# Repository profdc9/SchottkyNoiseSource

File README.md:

# Schottky Diode Noise Source

This is a schottky diode noise source that is based on the BAT17.  It is a project ready to be made at JLCPCB.

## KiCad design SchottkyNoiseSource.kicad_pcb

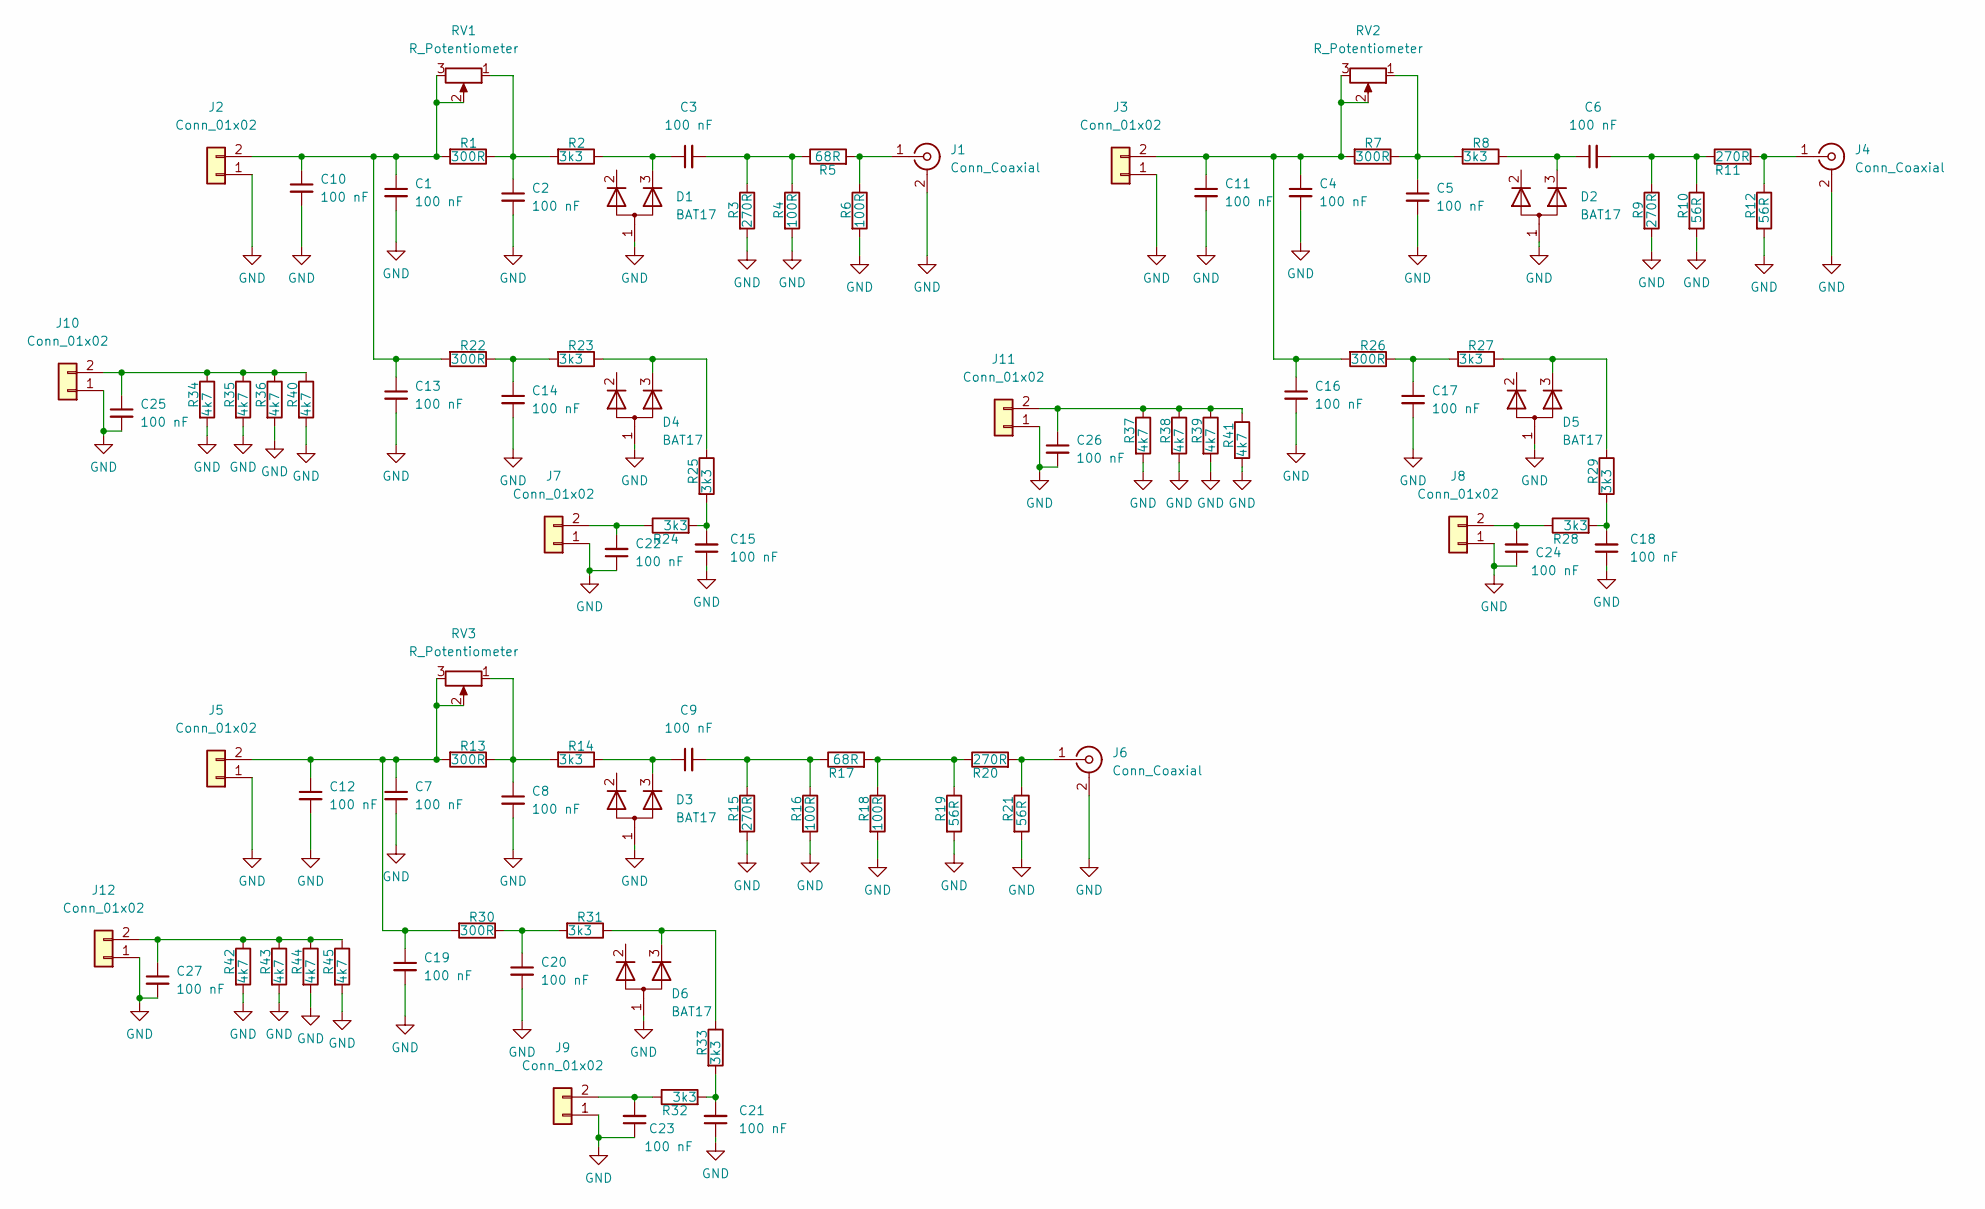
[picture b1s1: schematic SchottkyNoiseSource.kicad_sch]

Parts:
C1, C2, C3, C4, C5, C6, C7, C8, C9, C10, C11, C12, C13, C14, C15, C16, C17, C18, C19, C20, C21, C22, C23, C24, C25, C26, C27: 100 nF; C_0402_1005Metric_Pad0.74x0.62mm_HandSolder; LCSC C307331
D1, D2, D3, D4, D5, D6: BAT17; SOT-23; LCSC C456086
J1, J4, J6: Conn_Coaxial; SMA_Amphenol_132289_EdgeMount
J2, J3, J5, J7, J8, J9, J10, J11, J12: Conn_01x02; PinHeader_1x02_P2.54mm_Vertical
R1, R7, R13, R22, R26, R30: 300R; R_0805_2012Metric_Pad1.20x1.40mm_HandSolder; LCSC C17617
R2, R8, R14, R23, R24, R25, R27, R28, R29, R31, R32, R33: 3k3; R_0603_1608Metric_Pad0.98x0.95mm_HandSolder; LCSC C22978
R3, R9, R11, R15, R20: 270R; R_0603_1608Metric_Pad0.98x0.95mm_HandSolder; LCSC C22966
R4, R6, R16, R18: 100R; R_0603_1608Metric_Pad0.98x0.95mm_HandSolder; LCSC C22775
R5, R17: 68R; R_0603_1608Metric_Pad0.98x0.95mm_HandSolder; LCSC C27592
R10, R12, R19, R21: 56R; R_0603_1608Metric_Pad0.98x0.95mm_HandSolder; LCSC C25196
R34, R35, R36, R37, R38, R39, R40, R41, R42, R43, R44, R45: 4k7; R_1206_3216Metric_Pad1.30x1.75mm_HandSolder; LCSC C17936
RV1, RV2, RV3: R_Potentiometer; Potentiometer_Bourns_3296W_Vertical

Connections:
GND: C1.2, C2.2, C4.2, C5.2, C7.2, C8.2, C10.2, C11.2, C12.2, C13.2, C14.2, C15.1, C16.2, C17.2, C18.1, C19.2, C20.2, C21.1, C22.1, C23.1, C24.1, C25.2, C26.2, C27.2, D1.1 (A), D2.1 (A), D3.1 (A), D4.1 (A), D5.1 (A), D6.1 (A), J1.2 (Ext), J2.1, J3.1, J4.2 (Ext), J5.1, J6.2 (Ext), J7.1, J8.1, J9.1, J10.1, J11.1, J12.1, R3.2, R4.2, R6.2, R9.2, R10.2, R12.2, R15.2, R16.2, R18.2, R19.2, R21.2, R34.2, R35.2, R36.2, R37.2, R38.2, R39.2, R40.2, R41.2, R42.2, R43.2, R44.2, R45.2
unnamed: C1.1, C10.1, C13.1, J2.2, R1.2, R22.2, RV1.2, RV1.3
unnamed: C2.1, R1.1, R2.2, RV1.1
unnamed: C3.1, D1.3 (K), R2.1
unnamed: C3.2, R3.1, R4.1, R5.1
unnamed: C5.1, R7.1, R8.2, RV2.1
unnamed: C6.1, D2.3 (K), R8.1
unnamed: C6.2, R9.1, R10.1, R11.1
unnamed: C8.1, R13.1, R14.2, RV3.1
unnamed: C9.1, D3.3 (K), R14.1
unnamed: C9.2, R15.1, R16.1, R17.1
unnamed: C4.1, C11.1, C16.1, J3.2, R7.2, R26.2, RV2.2, RV2.3
unnamed: C7.1, C12.1, C19.1, J5.2, R13.2, R30.2, RV3.2, RV3.3
unnamed: C14.1, R22.1, R23.2
unnamed: C15.2, R24.2, R25.2
unnamed: C17.1, R26.1, R27.2
unnamed: C18.2, R28.2, R29.2
unnamed: C20.1, R30.1, R31.2
unnamed: C21.2, R32.2, R33.2
unnamed: C22.2, J7.2, R24.1
unnamed: C23.2, J9.2, R32.1
unnamed: C24.2, J8.2, R28.1
unnamed: C25.1, J10.2, R34.1, R35.1, R36.1, R40.1
unnamed: C26.1, J11.2, R37.1, R38.1, R39.1, R41.1
unnamed: C27.1, J12.2, R42.1, R43.1, R44.1, R45.1
unnamed: D4.3 (K), R23.1, R25.1
unnamed: D5.3 (K), R27.1, R29.1
unnamed: D6.3 (K), R31.1, R33.1
unnamed: J1.1 (In), R5.2, R6.1
unnamed: J4.1 (In), R11.2, R12.1
unnamed: J6.1 (In), R20.2, R21.1
unnamed: R17.2, R18.1, R19.1, R20.1

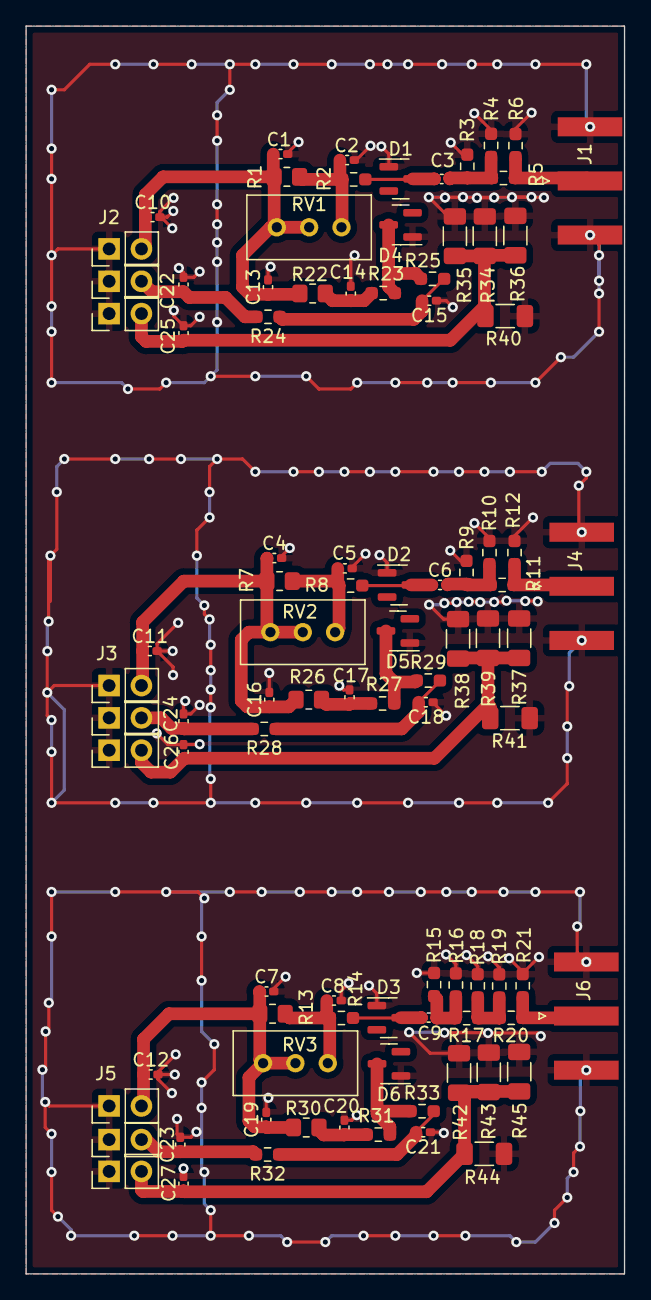
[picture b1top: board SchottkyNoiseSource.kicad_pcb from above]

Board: 2 copper layers, 47.0 x 98.0 mm, 93 parts (0 on the bottom side), 32 nets.

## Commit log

2023-07-12 Rearranged components slightly, removed solder mask to allow shield to be fitted
2023-07-15 Added sense diode to noise sources
2023-07-16 Added heater resistors
2023-07-19 Made pin header connector
